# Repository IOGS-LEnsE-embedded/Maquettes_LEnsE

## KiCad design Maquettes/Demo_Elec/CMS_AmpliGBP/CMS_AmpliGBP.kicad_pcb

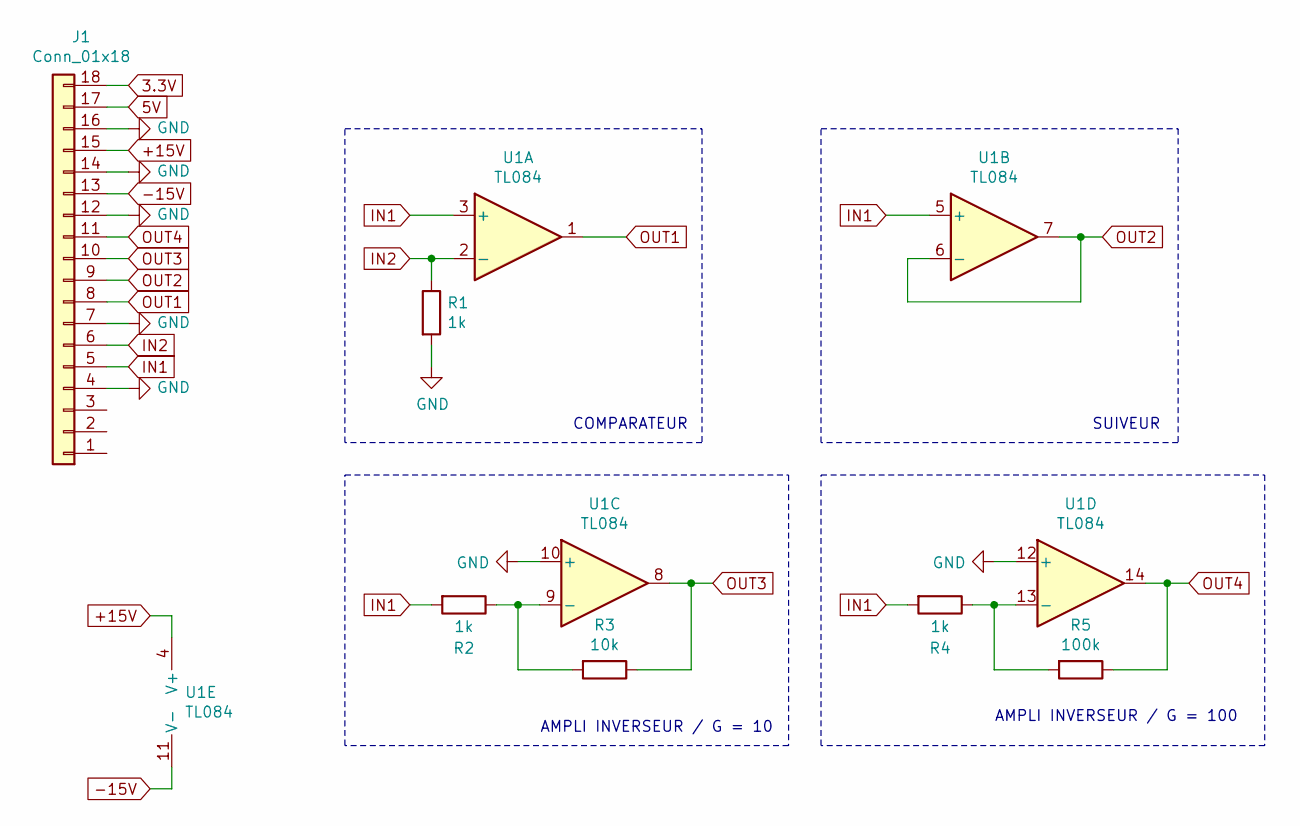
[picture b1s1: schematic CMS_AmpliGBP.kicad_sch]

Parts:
J1: Conn_01x18; PinHeader_1x18_P2.54mm_Horizontal
R1, R2, R4: 1k; R_0603_1608Metric
R3: 10k; R_0402_1005Metric
R5: 100k; R_0402_1005Metric
U1: TL084; SOIC-14_3.9x8.7mm_P1.27mm

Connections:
3.3V: J1.18
5V: J1.17
+15V: J1.15, U1.4 (V+)
-15V: J1.13, U1.11 (V-)
GND: J1.4, J1.7, J1.12, J1.14, J1.16, R1.2, U1.10 (+), U1.12 (+)
IN1: J1.5, R2.2, R4.2, U1.3 (+), U1.5 (+)
IN2: J1.6, R1.1, U1.2 (-)
unnamed: R2.1, R3.2, U1.9 (-)
unnamed: R4.1, R5.2, U1.13 (-)
OUT1: J1.8, U1.1
OUT2: J1.9, U1.6 (-), U1.7
OUT3: J1.10, R3.1, U1.8
OUT4: J1.11, R5.1, U1.14

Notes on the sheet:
SUIVEUR
AMPLI INVERSEUR / G = 10
AMPLI INVERSEUR / G = 100
COMPARATEUR

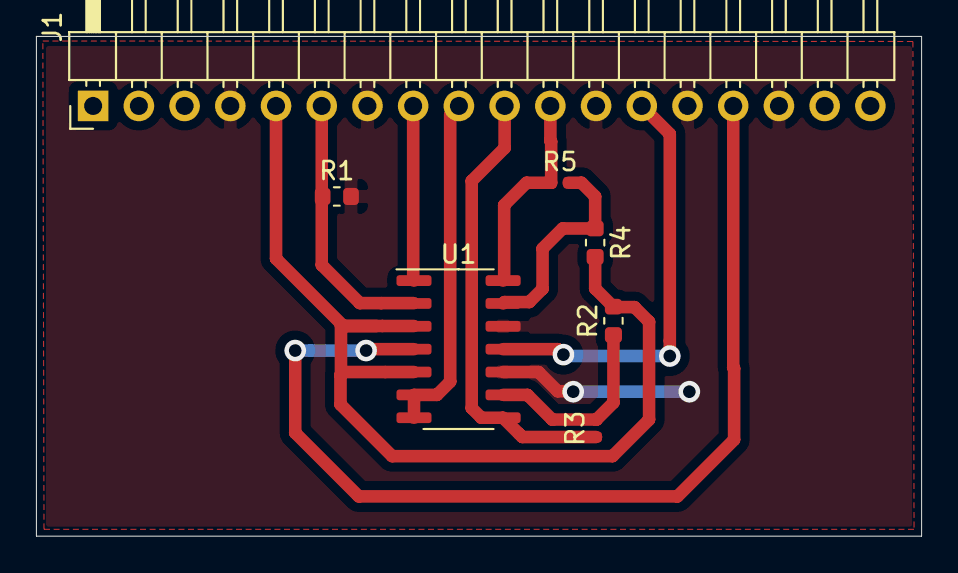
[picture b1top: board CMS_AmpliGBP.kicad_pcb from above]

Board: 2 copper layers, 49.2 x 27.8 mm, 7 parts (0 on the bottom side), 11 nets.

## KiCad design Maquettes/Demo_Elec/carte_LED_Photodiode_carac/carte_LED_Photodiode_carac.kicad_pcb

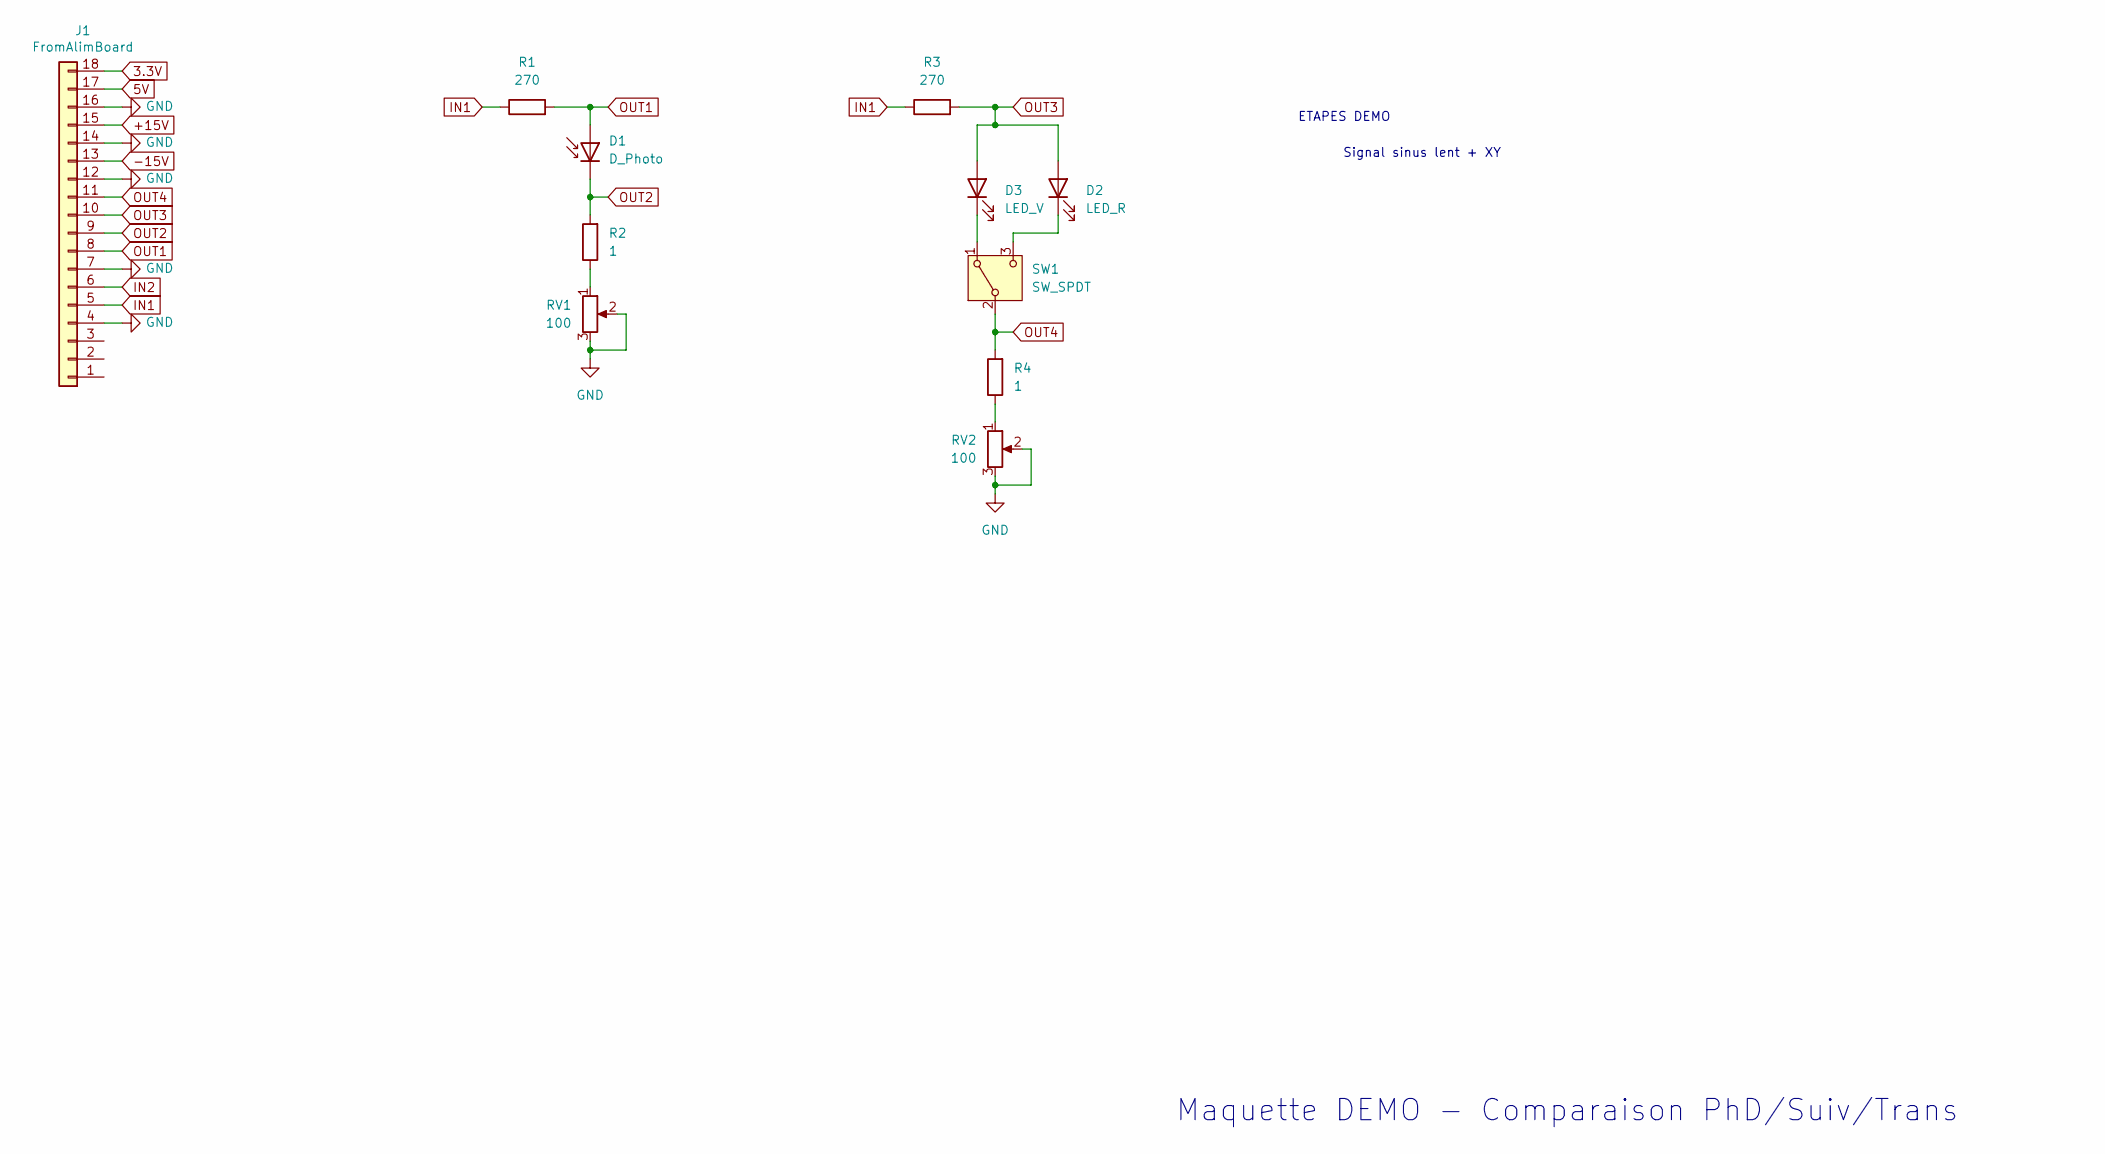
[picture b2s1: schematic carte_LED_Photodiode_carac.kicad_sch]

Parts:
D1: D_Photo; Osram_SFH205
D2: LED_R; LED_D5.0mm_Clear
D3: LED_V; LED_D5.0mm_Clear
J1: FromAlimBoard; PinHeader_1x18_P2.54mm_Horizontal
R1, R3: 270; R_Axial_DIN0207_L6.3mm_D2.5mm_P10.16mm_Horizontal
R2, R4: 1; R_Axial_DIN0207_L6.3mm_D2.5mm_P10.16mm_Horizontal
RV1, RV2: 100; Potentiometer_Vishay_T73YP_Vertical
SW1: SW_SPDT; Inter_SPDT

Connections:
3.3V: J1.18
5V: J1.17
+15V: J1.15
-15V: J1.13
GND: J1.4, J1.7, J1.12, J1.14, J1.16, RV1.2, RV1.3, RV2.2, RV2.3
IN1: J1.5, R1.1, R3.1
IN2: J1.6
unnamed: D2.1 (K), SW1.3 (C)
unnamed: D3.1 (K), SW1.1 (A)
unnamed: R2.1, RV1.1
unnamed: R4.1, RV2.1
OUT1: D1.2 (A), J1.8, R1.2
OUT2: D1.1 (K), J1.9, R2.2
OUT3: D2.2 (A), D3.2 (A), J1.10, R3.2
OUT4: J1.11, R4.2, SW1.2 (B)

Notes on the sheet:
ETAPES DEMO
Signal sinus lent + XY
Maquette DEMO - Comparaison PhD/Suiv/Trans

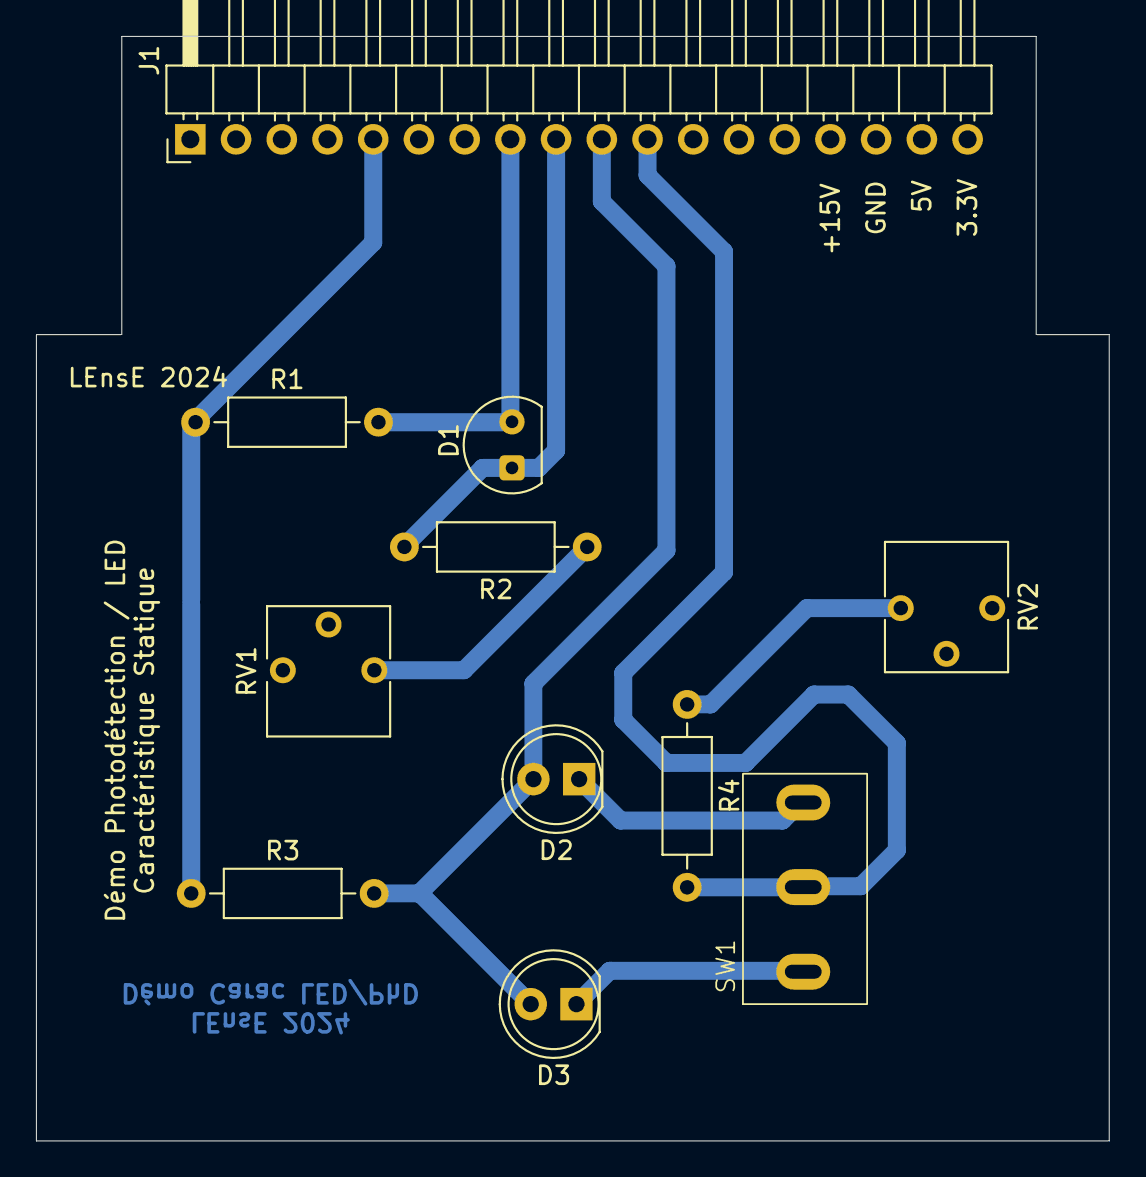
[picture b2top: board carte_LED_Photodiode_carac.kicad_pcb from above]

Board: 2 copper layers, 59.6 x 61.4 mm, 11 parts (0 on the bottom side), 10 nets.

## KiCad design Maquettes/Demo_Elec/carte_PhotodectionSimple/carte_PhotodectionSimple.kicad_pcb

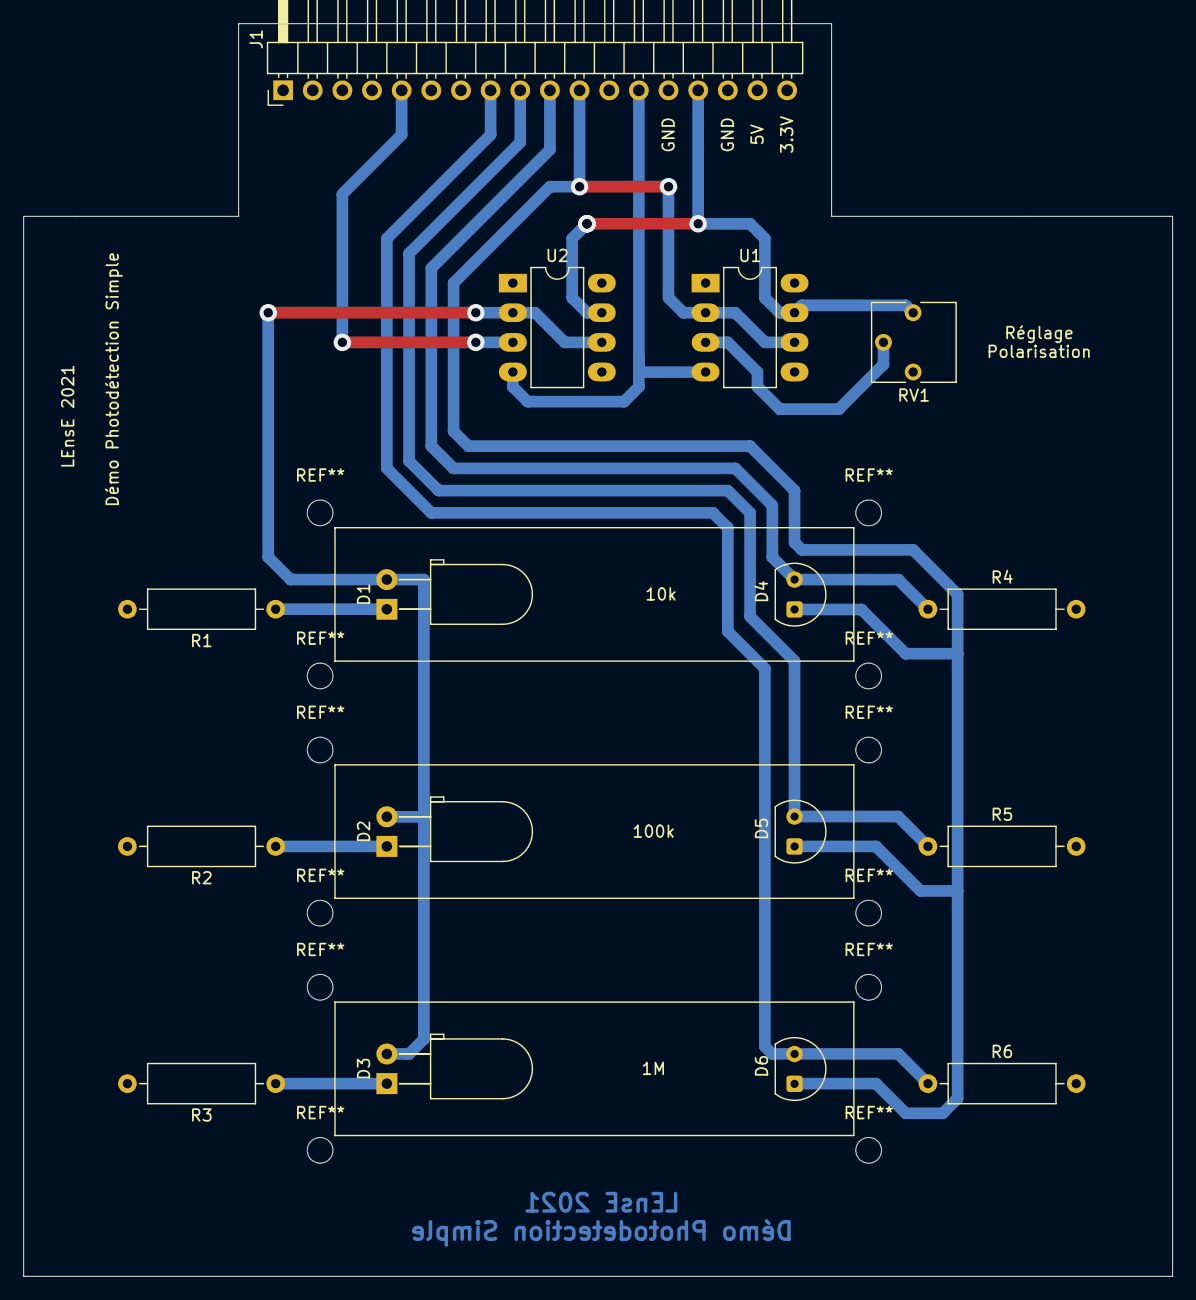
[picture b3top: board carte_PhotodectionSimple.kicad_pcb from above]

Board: 2 copper layers, 98.4 x 107.3 mm, 16 parts (0 on the bottom side), 13 nets.

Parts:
D1, D2, D3: LED; LED_D5.0mm_Horizontal_O3.81mm_Z9.0mm
D4, D5, D6: SFH206K; Osram_SFH206_2
J1: FromAlimBoard; PinHeader_1x18_P2.54mm_Horizontal
R1, R2, R3: 270; R_Axial_DIN0309_L9.0mm_D3.2mm_P12.70mm_Horizontal
R4: 10k; R_Axial_DIN0309_L9.0mm_D3.2mm_P12.70mm_Horizontal
R5: 100k; R_Axial_DIN0309_L9.0mm_D3.2mm_P12.70mm_Horizontal
R6: 1M; R_Axial_DIN0309_L9.0mm_D3.2mm_P12.70mm_Horizontal
RV1: 1k; Potentiometer_Vishay_T73YP_Vertical
U1: TL071; DIP-8_W7.62mm_LongPads
U2: OPA551; DIP-8_W7.62mm_LongPads

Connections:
+15V: J1.15, RV1.1, U1.7, U2.7
-15V: J1.13, U1.4, U2.4
GND: J1.4, J1.7, J1.12, J1.14, J1.16, R1.2, R2.2, R3.2, R4.2, R5.2, R6.2, RV1.3
IN1: J1.5, U2.3
LED_IN: D1.2, D2.2, D3.2, U2.2, U2.6
unnamed: D1.1, R1.1
unnamed: D2.1, R2.1
unnamed: D3.1, R3.1
unnamed: RV1.2, U1.3
OUT1: D6.2, J1.8, R6.1
OUT2: D5.2, J1.9, R5.1
OUT3: D4.2, J1.10, R4.1
OUT4: D4.1, D5.1, D6.1, J1.11, U1.2, U1.6

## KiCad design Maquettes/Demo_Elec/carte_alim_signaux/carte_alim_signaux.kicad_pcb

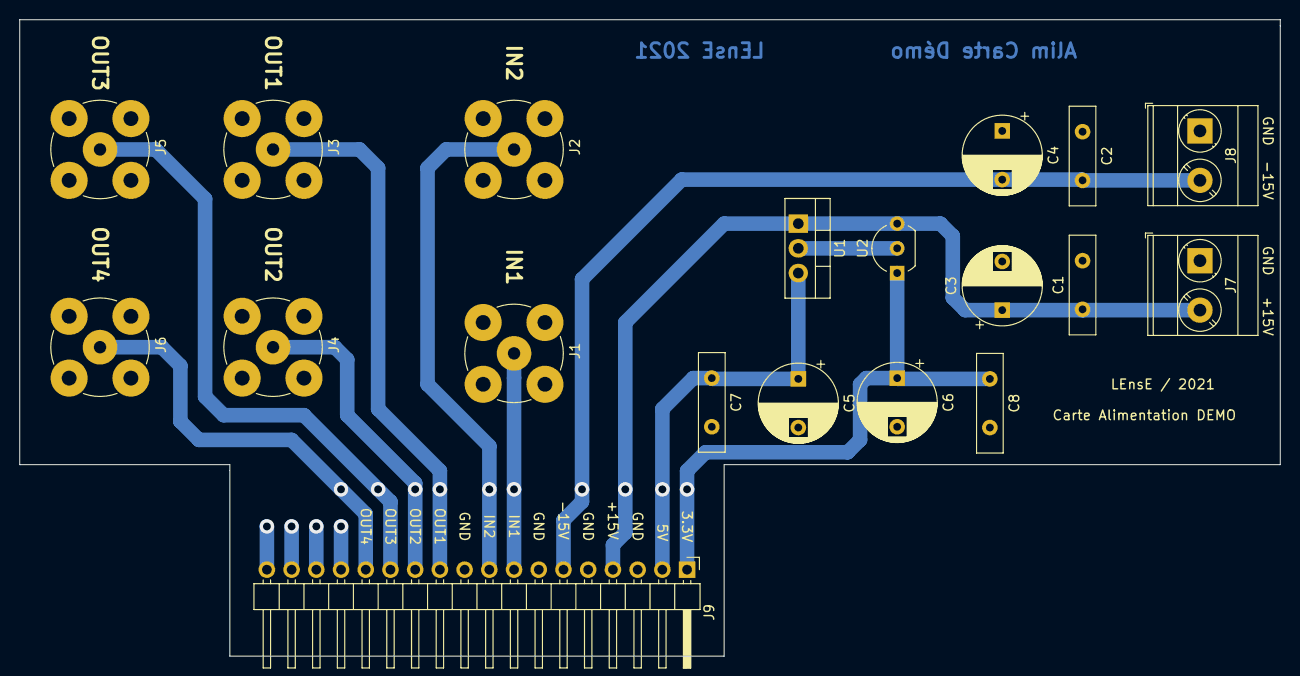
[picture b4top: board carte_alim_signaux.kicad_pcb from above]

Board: 2 copper layers, 129.5 x 65.4 mm, 19 parts (0 on the bottom side), 11 nets.

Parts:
C1, C2, C7, C8: 10n; C_Disc_D10.0mm_W2.5mm_P5.00mm
C3, C4, C5, C6: 10u; CP_Radial_D8.0mm_P5.00mm
J1: IN1_BNC; BNC_TEConnectivity_1478204_Vertical
J2: IN2_BNC; BNC_TEConnectivity_1478204_Vertical
J3: OUT1_BNC; BNC_TEConnectivity_1478204_Vertical
J4: OUT2_BNC; BNC_TEConnectivity_1478204_Vertical
J5: OUT3_BNC; BNC_TEConnectivity_1478204_Vertical
J6: OUT4_BNC; BNC_TEConnectivity_1478204_Vertical
J7, J8: Conn_01x02; TerminalBlock_Phoenix_MKDS-3-2-5.08_1x02_P5.08mm_Horizontal
J9: Conn_01x18; PinHeader_1x18_P2.54mm_Horizontal
U1: L7805; TO-220-3_Vertical
U2: L78L33_TO92; TO-92_Inline_Wide

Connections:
3.3V: C6.1, C8.1, J9.1, U2.1
5V: C5.1, C7.1, J9.2, U1.3
+15V: C1.1, C3.1, J7.2, J9.4, U1.1, U2.3
-15V: C2.2, C4.2, J8.2, J9.6
GND: C1.2, C2.1, C3.2, C4.1, C5.2, C6.2, C7.2, C8.2, J1.2, J2.2, J3.2, J4.2, J5.2, J6.2, J7.1, J8.1, J9.3, J9.5, J9.7, J9.10, J9.15, U1.2, U2.2
IN1: J1.1, J9.8
IN2: J2.1, J9.9
OUT1: J3.1, J9.11
OUT2: J4.1, J9.12
OUT3: J5.1, J9.13
OUT4: J6.1, J9.14

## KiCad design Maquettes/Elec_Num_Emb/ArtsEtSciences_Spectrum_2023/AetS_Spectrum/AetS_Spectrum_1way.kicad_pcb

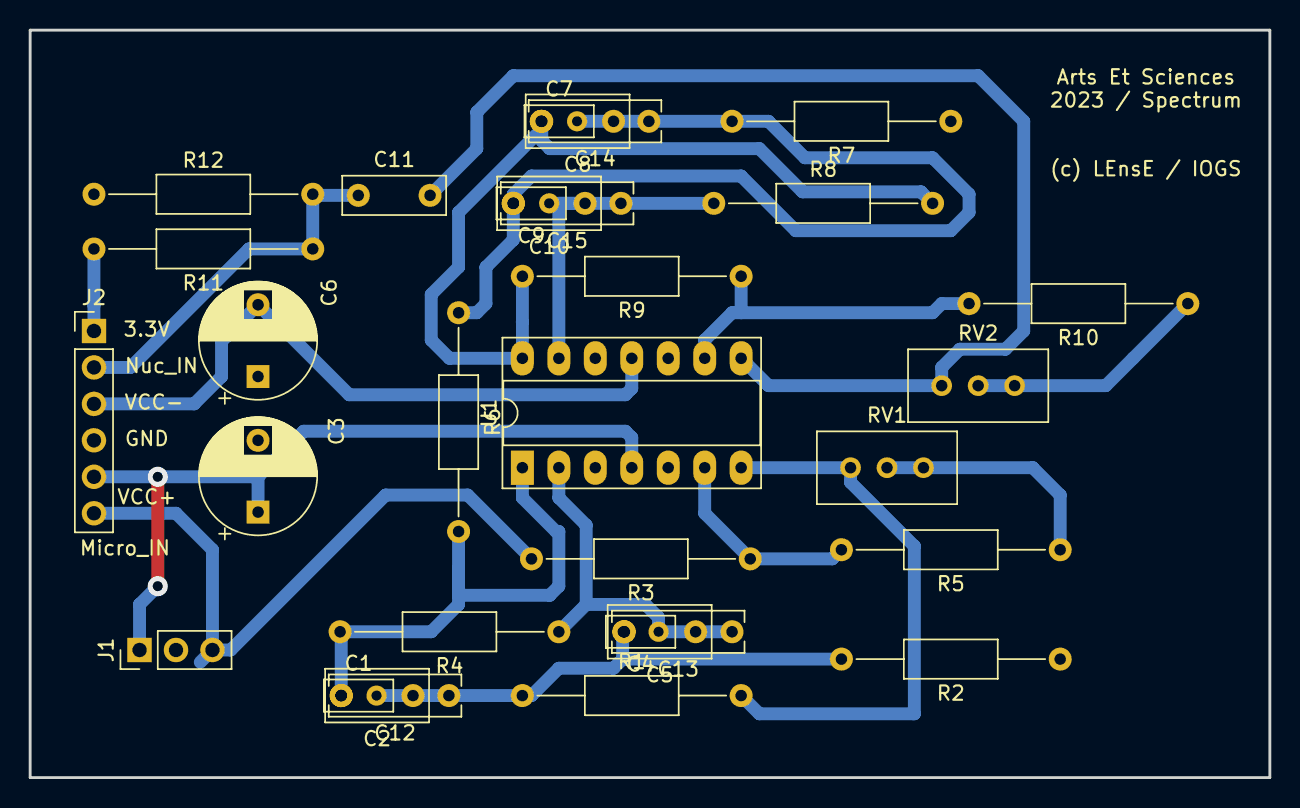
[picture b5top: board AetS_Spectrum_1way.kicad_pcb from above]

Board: 2 copper layers, 86.4 x 52.1 mm, 32 parts (0 on the bottom side), 18 nets.

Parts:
C1, C4, C7, C9: C; C_Rect_L4.6mm_W2.0mm_P2.50mm_MKS02_FKP02
C2, C5, C8, C10: C; C_Rect_L7.0mm_W3.5mm_P5.00mm
C3, C6: 100uF; CP_Radial_D8.0mm_P5.00mm
C11: 100nF; C_Rect_L7.0mm_W2.5mm_P5.00mm
C12, C13, C14, C15: C; C_Rect_L9.0mm_W2.7mm_P7.50mm_MKT
J1: Micro_test; PinHeader_1x03_P2.54mm_Vertical
J2: Conn_01x06; PinHeader_1x06_P2.54mm_Vertical
R1, R2, R4, R6, R7, R8: R; R_Axial_DIN0207_L6.3mm_D2.5mm_P15.24mm_Horizontal
R3, R9: 10k; R_Axial_DIN0207_L6.3mm_D2.5mm_P15.24mm_Horizontal
R5, R10: 1k; R_Axial_DIN0207_L6.3mm_D2.5mm_P15.24mm_Horizontal
R11, R12: 180k; R_Axial_DIN0207_L6.3mm_D2.5mm_P15.24mm_Horizontal
RV1, RV2: 100k; Potentiometer_Bourns_3296W_Vertical
U1: TL084; DIP-14_W7.62mm_Socket_LongPads

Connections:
3.3V: J2.1, R11.2
GND: C3.2, C6.1, J1.2, J2.4, R2.1, R7.1, R12.1, U1.3, U1.5, U1.10, U1.12
In_Nuc_B1: C11.1, J2.2, R11.1, R12.2
unnamed: C1.1, C2.2, C12.2, R4.2, R6.2, U1.1
unnamed: C1.2, C2.1, C4.2, C5.2, C12.1, C13.2, R1.1, R2.2
unnamed: C9.1, C10.1, C15.1, R8.1, U1.13
unnamed: C7.2, C8.1, C9.2, C10.2, C14.1, C15.2, R6.1, R7.2
unnamed: C4.1, C5.1, C13.1, R4.1, U1.2
unnamed: R3.1, R5.2, U1.6
unnamed: R5.1, RV1.1, RV1.2
unnamed: R10.1, RV2.1, RV2.2
unnamed: R9.1, R10.2, U1.9
Out_B1: C11.2, RV2.3, U1.8
Out_Filtre: C7.1, C8.2, C14.2, R8.2, R9.2, U1.14
VCC+: C3.1, J1.1, J2.5, U1.4
VCC-: C6.2, J2.3, U1.11
Vin_micro: J1.3, J2.6, R3.2
Vout_micro: R1.2, RV1.3, U1.7
